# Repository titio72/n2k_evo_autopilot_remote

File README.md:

# EvoAutoPilotRemote
RF remote for Raymarine EVO autopilots

The project uses a ESP32, a CAN adapter MCP2515 and a simple RF receiver to implement a remote command for Raymarine EVO Autopilots.
The remote I've used are simple, cheap EV1527 four buttons 433Mhz that you can find for a few euros on Amazon, Ebay etc.

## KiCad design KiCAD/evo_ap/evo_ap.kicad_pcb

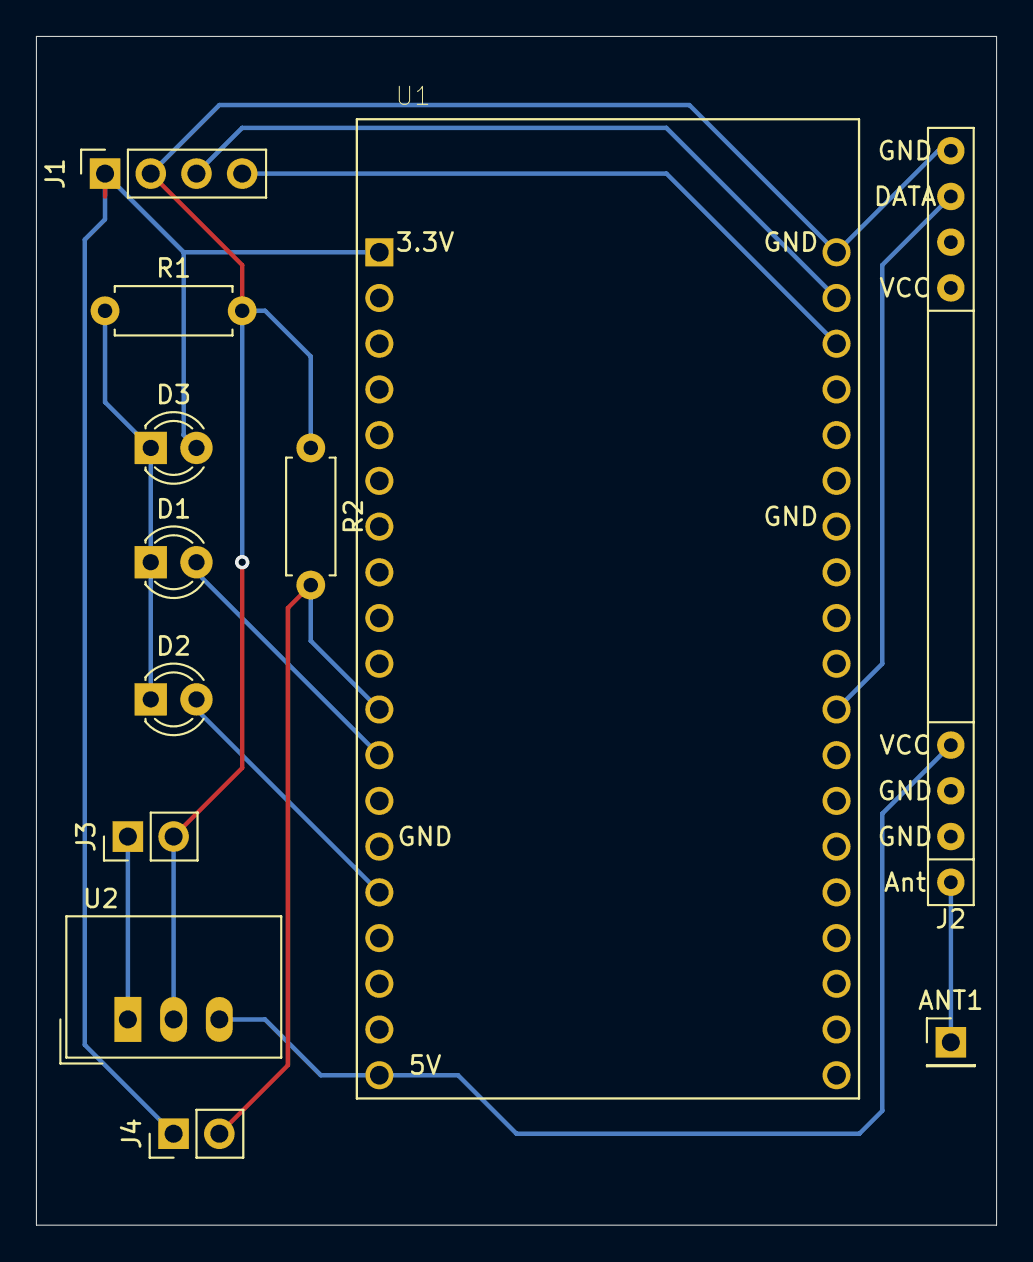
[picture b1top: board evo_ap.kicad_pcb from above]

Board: 2 copper layers, 53.3 x 66.0 mm, 12 parts (0 on the bottom side), 12 nets.

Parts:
ANT1: Conn_01x01; PinHeader_1x01_P2.54mm_Vertical
D1, D2, D3: LED; LED_D3.0mm
J1: SN65HVD230_01x04; PinSocket_1x04_P2.54mm_Vertical
J2: RXB6
J3, J4: Conn_01x02; PinHeader_1x02_P2.54mm_Vertical
R1, R2: R; R_Axial_DIN0207_L6.3mm_D2.5mm_P7.62mm_Horizontal
U1: ESP32-DEVKITC-32D; MODULE_ESP32-DEVKITC-32D
U2: TSR_1-2450; Converter_DCDC_TRACO_TSR-1_THT

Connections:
+12V: J3.1, U2.1
GND: J1.2, J2.8, J3.2, R1.2, R2.1, U1.20, U2.2
unnamed: ANT1.1, J2.1
unnamed: D1.1, D2.1, D3.1, R1.1
unnamed: D1.2, U1.12
unnamed: D2.2, U1.15
unnamed: D3.2, J1.1, J4.1, U1.1
unnamed: J1.3, U1.21
unnamed: J1.4, U1.22
unnamed: J2.4, U1.19, U2.3
unnamed: J2.7, U1.30
unnamed: J4.2, R2.2, U1.11

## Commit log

2021-04-29 removed unused functions
2021-04-30 Added support for programming remote
2021-05-01 debug flag (to test withou AP)
2021-05-02 Field tests changes
2021-05-03 Testing SN65HVD230 instead of MCP2515
2021-05-05 Added "define" for hw configuration
2021-05-05 cleanup
2021-05-07 Added support for bluetooth
2021-05-13 Improved logging
2021-05-14 Changed loop pause from 100 to 10ms
2021-05-20 BT enhancements
2021-05-26 Added support to oled display
2021-05-31 Added support for Wind Vane
2021-06-03 Schema update using MCP2562
